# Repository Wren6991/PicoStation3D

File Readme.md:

PicoStation 3D
==============

This is an **unfinished, untested** project to develop a 3D games console based on an RP2040 microcontroller and an iCE40 UP5k FPGA. Quick links:

- [Board Schematic (PDF)](board/picostation.pdf)
- [RP2040 Datasheet (PDF)](https://datasheets.raspberrypi.org/rp2040/rp2040-datasheet.pdf)
- [FPGA Datasheet (PDF)](http://www.latticesemi.com/-/media/LatticeSemi/Documents/DataSheets/iCE/iCE40-UltraPlus-Family-Data-Sheet.ashx)

From left to right, the components on the top edge are:

- A 3.5mm TRS audio jack, connected straight to RP2040 GPIOs via an RC filter (no separate audio supply on this board rev)
- A status LED for the RP2040
- A micro SD receptacle connected to the RP2040
- A micro USB socket providing power to the board, and code download and serial comms via the RP2040
- A status LED for the FPGA
- An HDMI socket for DVI-D video output, connected to the FPGA

The bottom edge has two SNES controller sockets. Also on the board is an 8MiB HyperRAM connected to the FPGA.

There is a RESET and BOOTSEL button for the RP2040, for quick firmware updates over USB, but the debug header (UART + SWD) is a better solution for iterating and developing code.

There are 12 wires connecting the FPGA to the microcontroller, one of them going from a GPOUT clock output on the RP2040 to a GB_IN global clock input pin on the UP5k. The intention is to use these for an 8 bit parallel bus with a free-running clock, a valid-ready handshake and an IRQ line, and for the UP5k to derive its internal clocks from the bus clock. This interface overlaps with the pins required to load the FPGA's internal configuration memory (and the RP2040 also has control of the UP5k's reset) so there is no separate external flash required for the UP5k.

Board Use Cases
---------------

- Run everything, including graphics routines, on RP2040, and use the UP5k as a parallel to DVI-D bridge -- [see here for a quick demo of some scanline blitting on RP2040](https://twitter.com/wren6991/status/1352983731661926401?s=20)

- Run everything, including a soft processor, on the UP5k, and use RP2040 as a surprisingly cost-effective USB-serial bridge, as well as for firmware upload. You'll need some kind of shell running on the RP2040 to provide audio and controller port access from the FPGA

- Run game logic, audio, controller access and SD card access on RP2040, put all the graphics hardware in the UP5k (with the local 8MB HyperRAM as VRAM, plus the UP5k's internal 128k SPRAM)

- Run 3D vertex-side operations on RP2040, and put 3D fragment-side hardware on the FPGA

Project Status
--------------

I've laid out a first iteration of the board, and have soldered up a prototype, but haven't had the chance to bring up the board or write any firmware, thanks to being a bit overloaded with the launch of RP2040 itself!

There are questionable decisions in [the schematic](board/picostation.pdf) (in particular the power chain violates the UP5k's sequencing requirements) so you shouldn't copy what you see here, but I'm posting this anyway because it might inspire somebody to make something better, and that is more important than me being embarrassed about my shoddy design work.

You can find a proof of concept for direct DVI output from a UP5k FPGA [in this repo](https://github.com/Wren6991/smoldvi).

I've also managed to squeeze [RISCBoy](https://github.com/Wren6991/RISCBoy) plus a DVI output onto a UP5k. Still need to push that code but you can see [a video of it I tweeted](https://twitter.com/wren6991/status/1348722305720004608?s=20). This shows you can fit plenty of interesting graphics hardware (and in this case a RISC-V processor) into a UP5k whilst generating DVI-D signals.

Known issues with rev A:

- Digital supply noise is audible through the audio jack. This could be improved by a separate LDO'd audio supply with a dual logic buffer, or just by deleting this output and doing digital audio through the video connector on the FPGA.
- The FPGA core supply comes from RP2040's LDO, to try and keep part count to an absolute minimum. This gives a fast ramp to 1.1 V shortly *after* the 3.3 V IO supply comes up, and a second ramp to 1.2 V some milliseconds later when software adjusts RP2040's core regulator. This is all quite questionable, and part of the point of Rev A is to find out whether I can get away with this.
- The controllers are only accessible from RP2040, not the FPGA. This is not a huge issue, but it would be more fun as an FPGA platform if they were moved to the FPGA, or perhaps even make the CLK and LAT line open-drain, and connect the controllers to both FPGA *and* RP2040.
- There is no separate configuration flash for the FPGA. Instead the microcontroller stores the bitstream in its flash, and writes this into the FPGA's configuration memory at boot. This should work fine but it's a less familiar development flow for those using this as an FPGA board, and it might be nice for pure-FPGA games consoles to have some local flash to access. Again, I'm trying to see how little hardware I can get away with, and this might have been a misstep.
- The SNES controller sockets are transposed left-to-right compared with an actual SNES.
- Double-sided component load makes it annoying to reflow this board at home, and adds cost if you want to get it PCBA'd.

If you have read all the way to the end and you have spotted something else that irritates you about this design, please [raise an issue!](/../../issues/) It will be a while until I get to Rev B. The main purpose of Rev A was to explore what I could get away with, and to develop the comms and interactions between microcontroller and FPGA.

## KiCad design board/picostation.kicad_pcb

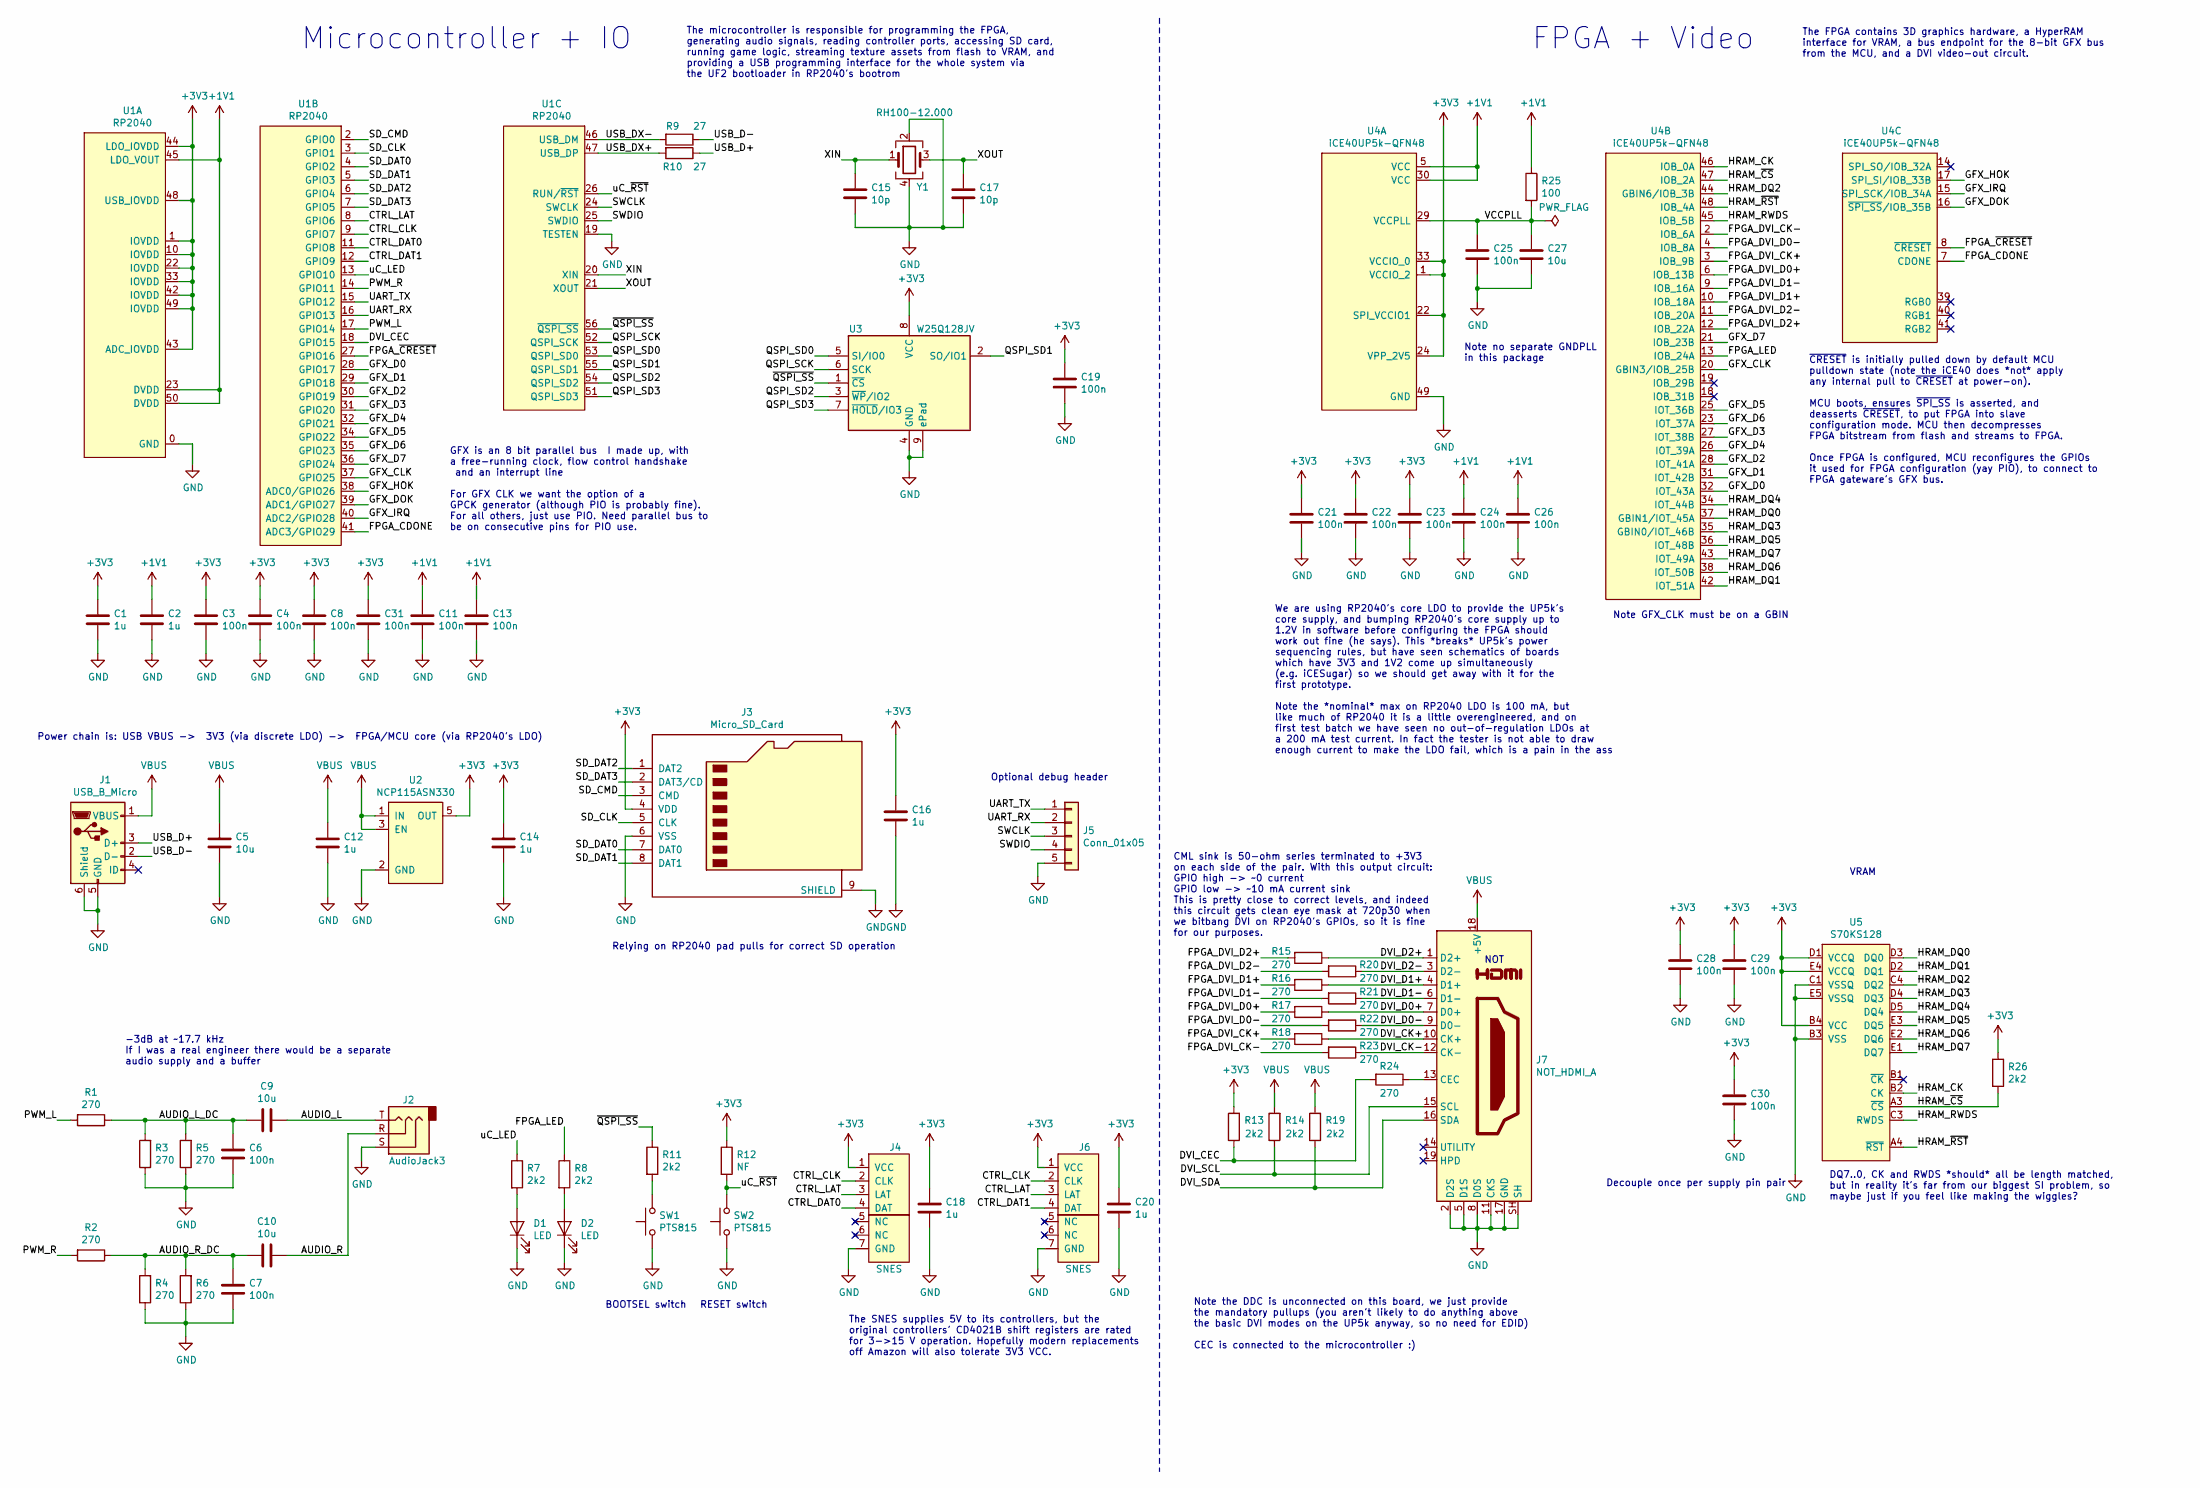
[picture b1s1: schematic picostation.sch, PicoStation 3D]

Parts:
C1, C2, C12, C14, C16, C18, C20: 1u; C_0402_1005Metric
C3, C4, C6, C7, C8, C11, C13, C19, C21, C22, C23, C24, C25, C26, C28, C29, C30, C31: 100n; C_0402_1005Metric
C5, C9, C10, C27: 10u; C_0603_1608Metric
C15, C17: 10p; C_0402_1005Metric
D1, D2: LED; LED_0603_1608Metric
J1: USB_B_Micro; USB_Micro-B_Molex-105017-0001
J2: AudioJack3; STX-3000-TRS
J3: Micro_SD_Card; MEM2061-MICRO-SD
J4: SNES; SNES-Controller-Right
J5: Conn_01x05; PinHeader_1x05_P2.54mm_Vertical
J6: SNES; SNES-Controller-Left
J7: NOT_HDMI_A; HDMI-SS-53000
R1, R2, R3, R4, R5, R6, R15, R16, R17, R18, R20, R21, R22, R23, R24: 270; R_0402_1005Metric
R7, R8, R11, R13, R14, R19, R26: 2k2; R_0402_1005Metric
R9, R10: 27; R_0402_1005Metric
R12: NF; R_0402_1005Metric
R25: 100; R_0402_1005Metric
SW1, SW2: PTS815; SW_SPST_PTS815
U1: RP2040; QFN-56_EP_7x7_Pitch0.4mm
U2: NCP115ASN330; SOT-23-5
U3: W25Q128JV; WSON-8-1EP_6x5mm_P1.27mm_EP3.4x4mm
U4: iCE40UP5k-QFN48; QFN-48-1EP_7x7mm_P0.5mm_EP5.3x5.3mm
U5: S70KS128
Y1: RH100-12.000; Crystal_SMD_3225-4Pin_3.2x2.5mm

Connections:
+1V1: C2.1, C11.1, C13.1, C24.1, C26.1, R25.1, U1.23 (DVDD), U1.45 (LDO_VOUT), U1.50 (DVDD), U4.5 (VCC), U4.30 (VCC)
+3V3: C1.1, C3.1, C4.1, C8.1, C14.1, C16.1, C18.1, C19.1, C20.1, C21.1, C22.1, C23.1, C28.1, C29.1, C30.1, C31.1, J3.4 (VDD), J4.1 (VCC), J6.1 (VCC), R12.1, R13.2, R26.1, U1.1 (IOVDD), U1.10 (IOVDD), U1.22 (IOVDD), U1.33 (IOVDD), U1.42 (IOVDD), U1.43 (ADC_IOVDD), U1.44 (LDO_IOVDD), U1.48 (USB_IOVDD), U1.49 (IOVDD), U2.5 (OUT), U3.8 (VCC), U4.1 (VCCIO_2), U4.22 (SPI_VCCIO1), U4.24 (VPP_2V5), U4.33 (VCCIO_0), U5.B4 (VCC), U5.D1 (VCCQ), U5.E4 (VCCQ)
/AUDIO_L: C9.1, J2.T
/AUDIO_L_DC: C6.1, C9.2, R1.1, R3.2, R5.2
/AUDIO_R: C10.1, J2.R
/AUDIO_R_DC: C7.1, C10.2, R2.1, R4.2, R6.2
/CTRL_CLK: J4.2 (CLK), J6.2 (CLK), U1.9 (GPIO7)
/CTRL_DAT0: J4.4 (DAT), U1.11 (GPIO8)
/CTRL_DAT1: J6.4 (DAT), U1.12 (GPIO9)
/CTRL_LAT: J4.3 (LAT), J6.3 (LAT), U1.8 (GPIO6)
/DVI_CEC: R13.1, R24.2, U1.18 (GPIO15)
/DVI_CK+: J7.10 (CK+), R18.1
/DVI_CK-: J7.12 (CK-), R23.1
/DVI_D0+: J7.7 (D0+), R17.1
/DVI_D0-: J7.9 (D0-), R22.1
/DVI_D1+: J7.4 (D1+), R16.1
/DVI_D1-: J7.6 (D1-), R21.1
/DVI_D2+: J7.1 (D2+), R15.1
/DVI_D2-: J7.3 (D2-), R20.1
/DVI_SCL: J7.15 (SCL), R14.1
/DVI_SDA: J7.16 (SDA), R19.1
/FPGA_CDONE: U1.41 (ADC3/GPIO29), U4.7 (CDONE)
/FPGA_DVI_CK+: R18.2, U4.3 (IOB_9B)
/FPGA_DVI_CK-: R23.2, U4.2 (IOB_6A)
/FPGA_DVI_D0+: R17.2, U4.6 (IOB_13B)
/FPGA_DVI_D0-: R22.2, U4.4 (IOB_8A)
/FPGA_DVI_D1+: R16.2, U4.10 (IOB_18A)
/FPGA_DVI_D1-: R21.2, U4.9 (IOB_16A)
/FPGA_DVI_D2+: R15.2, U4.12 (IOB_22A)
/FPGA_DVI_D2-: R20.2, U4.11 (IOB_20A)
/FPGA_LED: R8.1, U4.13 (IOB_24A)
/FPGA_~CRESET~: U1.27 (GPIO16), U4.8 (~CRESET~)
/GFX_CLK: U1.37 (GPIO25), U4.20 (GBIN3/IOB_25B)
/GFX_D0: U1.28 (GPIO17), U4.32 (IOT_43A)
/GFX_D1: U1.29 (GPIO18), U4.31 (IOT_42B)
/GFX_D2: U1.30 (GPIO19), U4.28 (IOT_41A)
/GFX_D3: U1.31 (GPIO20), U4.27 (IOT_38B)
/GFX_D4: U1.32 (GPIO21), U4.26 (IOT_39A)
/GFX_D5: U1.34 (GPIO22), U4.25 (IOT_36B)
/GFX_D6: U1.35 (GPIO23), U4.23 (IOT_37A)
/GFX_D7: U1.36 (GPIO24), U4.21 (IOB_23B)
/GFX_DOK: U1.39 (ADC1/GPIO27), U4.16 (~SPI_SS~/IOB_35B)
/GFX_HOK: U1.38 (ADC0/GPIO26), U4.17 (SPI_SI/IOB_33B)
/GFX_IRQ: U1.40 (ADC2/GPIO28), U4.15 (SPI_SCK/IOB_34A)
/HRAM_CK: U4.46 (IOB_0A), U5.B2 (CK)
/HRAM_DQ0: U4.37 (GBIN1/IOT_45A), U5.D3 (DQ0)
/HRAM_DQ1: U4.42 (IOT_51A), U5.D2 (DQ1)
/HRAM_DQ2: U4.44 (GBIN6/IOB_3B), U5.C4 (DQ2)
/HRAM_DQ3: U4.35 (GBIN0/IOT_46B), U5.D4 (DQ3)
/HRAM_DQ4: U4.34 (IOT_44B), U5.D5 (DQ4)
/HRAM_DQ5: U4.36 (IOT_48B), U5.E3 (DQ5)
/HRAM_DQ6: U4.38 (IOT_50B), U5.E2 (DQ6)
/HRAM_DQ7: U4.43 (IOT_49A), U5.E1 (DQ7)
/HRAM_RWDS: U4.45 (IOB_5B), U5.C3 (RWDS)
/HRAM_~CS~: R26.2, U4.47 (IOB_2A), U5.A3 (~CS~)
/HRAM_~RST~: U4.48 (IOB_4A), U5.A4 (~RST~)
/PWM_L: R1.2, U1.17 (GPIO14)
/PWM_R: R2.2, U1.14 (GPIO11)
/QSPI_SCK: U1.52 (QSPI_SCK), U3.6 (SCK)
/QSPI_SD0: U1.53 (QSPI_SD0), U3.5 (SI/IO0)
/QSPI_SD1: U1.55 (QSPI_SD1), U3.2 (SO/IO1)
/QSPI_SD2: U1.54 (QSPI_SD2), U3.3 (~WP~/IO2)
/QSPI_SD3: U1.51 (QSPI_SD3), U3.7 (~HOLD~/IO3)
/SD_CLK: J3.5 (CLK), U1.3 (GPIO1)
/SD_CMD: J3.3 (CMD), U1.2 (GPIO0)
/SD_DAT0: J3.7 (DAT0), U1.4 (GPIO2)
/SD_DAT1: J3.8 (DAT1), U1.5 (GPIO3)
/SD_DAT2: J3.1 (DAT2), U1.6 (GPIO4)
/SD_DAT3: J3.2 (DAT3/CD), U1.7 (GPIO5)
/SWCLK: J5.3, U1.24 (SWCLK)
/SWDIO: J5.4, U1.25 (SWDIO)
/UART_RX: J5.2, U1.16 (GPIO13)
/UART_TX: J5.1, U1.15 (GPIO12)
/USB_D+: J1.3 (D+), R10.1
/USB_D-: J1.2 (D-), R9.1
/USB_DX+: R10.2, U1.47 (USB_DP)
/USB_DX-: R9.2, U1.46 (USB_DM)
/VCCPLL: C25.1, C27.1, R25.2, U4.29 (VCCPLL)
/XIN: C15.1, U1.20 (XIN), Y1.1
/XOUT: C17.1, U1.21 (XOUT), Y1.3
/uC_LED: R7.1, U1.13 (GPIO10)
/uC_~RST~: R12.2, SW2.2, U1.26 (RUN/~RST~)
/~QSPI_SS~: R11.1, U1.56 (~QSPI_SS~), U3.1 (~CS)
GND: C1.2, C2.2, C3.2, C4.2, C5.2, C6.2, C7.2, C8.2, C11.2, C12.2, C13.2, C14.2, C15.2, C16.2, C17.2, C18.2, C19.2, C20.2, C21.2, C22.2, C23.2, C24.2, C25.2, C26.2, C27.2, C28.2, C29.2, C30.2, C31.2, D1.1 (K), D2.1 (K), J1.5 (GND), J1.6 (Shield), J2.S, J3.6 (VSS), J3.9 (SHIELD), J4.7 (GND), J5.5, J6.7 (GND), J7.2 (D2S), J7.5 (D1S), J7.8 (D0S), J7.11 (CKS), J7.17 (GND), J7.SH, R3.1, R4.1, R5.1, R6.1, SW1.1, SW2.1, U1.0 (GND), U1.19 (TESTEN), U2.2 (GND), U3.4 (GND), U3.9 (ePad), U4.49 (GND), U5.B3 (VSS), U5.C1 (VSSQ), U5.E5 (VSSQ), Y1.2, Y1.4
unnamed: D1.2 (A), R7.2
unnamed: D2.2 (A), R8.2
unnamed: J7.13 (CEC), R24.1
unnamed: R11.2, SW1.2
VBUS: C5.1, C12.1, J1.1 (VBUS), J7.18 (+5V), R14.2, R19.2, U2.1 (IN), U2.3 (EN)

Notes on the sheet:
Decouple once per supply pin pair
DQ7..0, CK and RWDS *should* all be length matched, but in reality it's far from our biggest SI problem, so maybe just if you feel like making the wiggles?
Note no separate GNDPLL in this package
We are using RP2040's core LDO to provide the UP5k's core supply, and bumping RP2040's core supply up to 1.2V in software before configuring the FPGA should work out fine (he says). This *breaks* UP5k's power sequencing rules, but have seen schematics of boards which have 3V3 and 1V2 come up simult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
NOT
GFX is an 8 bit parallel bus I made up, with a free-running clock, flow control handshake and an interrupt line For GFX CLK we want the option of a GPCK generator (although PIO is probably fine). For all others, just use PIO. Need parallel bus to be on consecutive pins for PIO use.
BOOTSEL switch
RESET switch
-3dB at ~~17.7 kHz If I was a real engineer there would be a separate audio supply and a buffer
The SNES supplies 5V to its controllers, but the original controllers' CD4021B shift registers are rated for 3->15 V operation. Hopefully modern replacements off Amazon will also tolerate 3V3 VCC.
FPGA + Video
Microcontroller + IO
Power chain is: USB VBUS -> 3V3 (via discrete LDO) -> FPGA/MCU core (via RP2040's LDO)
~CRESET~ is initially pulled down by default MCU pulldown state (note the iCE40 does *not* apply any internal pull to ~CRESET~ at power-on). MCU boots, ensures ~SPI_SS~ is asserted, and deasserts ~CRESET~, to put FPGA into slave configuration mode. MCU then decompresses FPGA bitstream from flash an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
Relying on RP2040 pad pulls for correct SD operation
VRAM
CML sink is 50-ohm series terminated to +3V3 on each side of the pair. With this output circuit: GPIO high -> ~~0 current GPIO low -> ~~10 mA current sink This is pretty close to correct levels, and indeed this circuit gets clean eye mask at 720p30 when we bitbang DVI on RP2040's GPIOs, so it is fi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
The FPGA contains 3D graphics hardware, a HyperRAM interface for VRAM, a bus endpoint for the 8-bit GFX bus from the MCU, and a DVI video-out circuit.
The microcontroller is responsible for programming the FPGA, generating audio signals, reading controller ports, accessing SD card, running game logic, streaming texture assets from flash to VRAM, and providing a USB programming interface for the whole system via the UF2 bootloader in RP2040's boot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
Optional debug header
Note GFX_CLK must be on a GBIN
Note the DDC is unconnected on this board, we just provide the mandatory pullups (you aren't likely to do anything above the basic DVI modes on the UP5k anyway, so no need for EDID) CEC is connected to the microcontroller :)

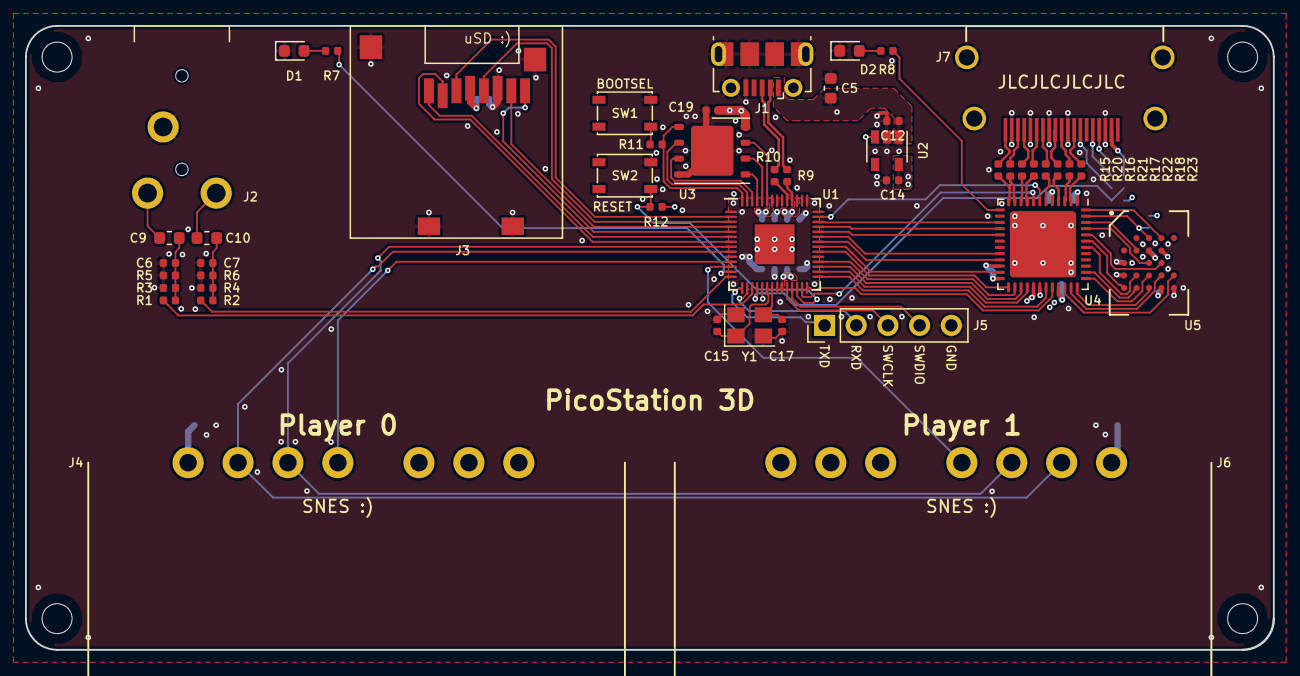
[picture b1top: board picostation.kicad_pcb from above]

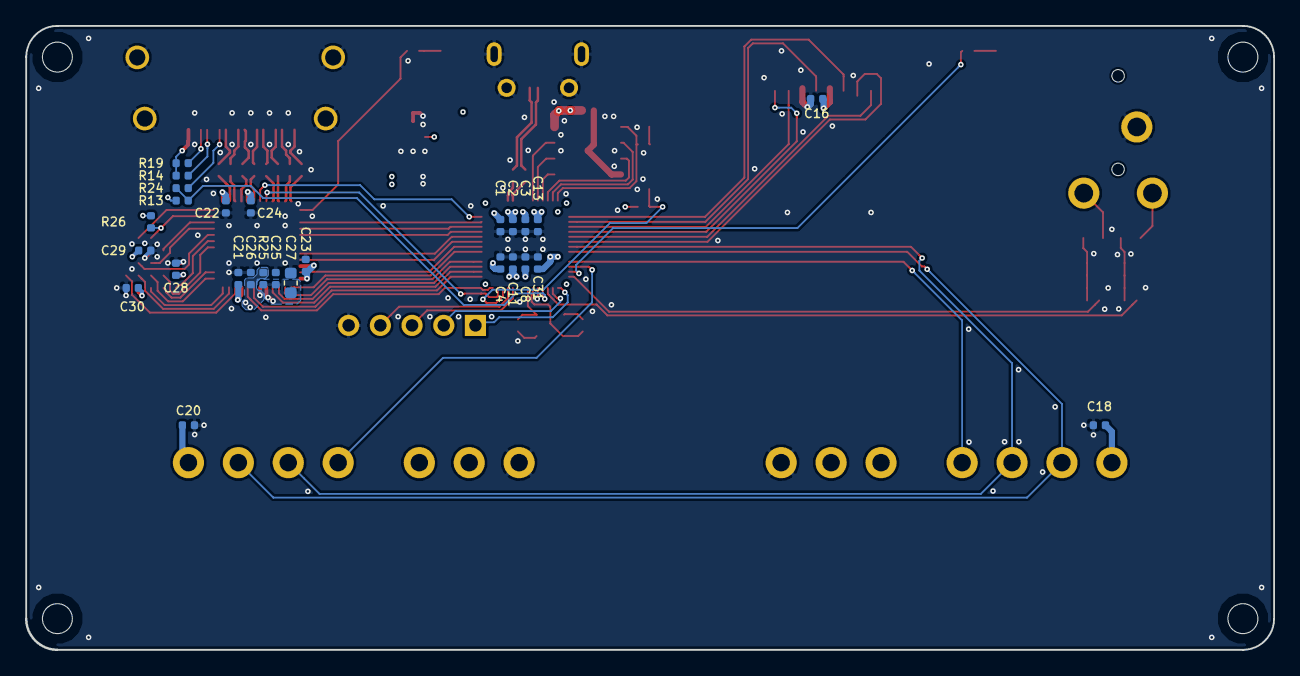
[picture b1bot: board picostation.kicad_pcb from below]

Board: 4 copper layers, 100.0 x 50.0 mm, 74 parts (27 on the bottom side), 89 nets.

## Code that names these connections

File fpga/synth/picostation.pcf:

# Blink blonk
set_io led 13

# HyperRAM
set_io hram_clk   46
set_io hram_cs_n  47
set_io hram_rst_n 48
set_io hram_rwds  45
set_io hram_dq[0] 37
set_io hram_dq[1] 42
set_io hram_dq[2] 44
set_io hram_dq[3] 35
set_io hram_dq[4] 34
set_io hram_dq[5] 36
set_io hram_dq[6] 38
set_io hram_dq[7] 43

# GFX-bus host interface (including our main clock source)
set_io gfx_clk   20
set_io gfx_dok   16
set_io gfx_hok   17
set_io gfx_irq   15
set_io gfx_dq[0] 32
set_io gfx_dq[1] 31
set_io gfx_dq[2] 28
set_io gfx_dq[3] 27
set_io gfx_dq[4] 26
set_io gfx_dq[5] 25
set_io gfx_dq[6] 23
set_io gfx_dq[7] 21

# DVI interface (lane order {CLK, D2, D1, D0})
set_io dvi_p[3] 3
set_io dvi_n[3] 2
set_io dvi_p[2] 12
set_io dvi_n[2] 11
set_io dvi_p[1] 10
set_io dvi_n[1] 9
set_io dvi_p[0] 6
set_io dvi_n[0] 4

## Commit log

2021-02-06 Play with PWM audio
2021-02-06 make "unfinished, untested" bold in readme :)
2021-02-06 Expand project status section in readme
2021-02-14 Add libfpga and fpgascripts to submodules
2021-02-14 Wrong pin number for CDONE
2021-02-14 Plausible looking init sequence for UP5k. Still doesn't want to talk to me
